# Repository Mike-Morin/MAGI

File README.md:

## 363_Electrode
Electrode array with 3 input neuron contacts, 6 hidden layer contacts, and 3 output neuron contacts with dual input and output contacts for excitatory and inhibitory input and output neurons. Fits on a standard compound microscope stage and supports 12mm round coverslips for the electrode arrays.

## PetriDish
A chemotaxis game to be interfaced with a physical neural network using the Analog Discovery 2 API. Intended to train a network using reinforcement learning. An agent must follow concentration gradients to food in order to replenish energy. You can play it too.

## pnn_cs_driver
A 4 channel precision voltage controlled current source. 1mA/V, biploar 5mA+/-20nA output with 18V compliance voltage, <10ppm, 3.5 MHz bandwdith.

## SMU Test Fixture (In Progress)
16-Channel source measure unit with multiplexer for the Analog Discovery 2 (AD2). Intended to interface with a 32 pin electrode array. 

## SMU Shunt Amp (In Progress)
 - Prototype board for high speed, precision SMU Test Fixture current shunt amp.
 
## 20 Pin Electrode Connector
Pogo pin connector to bare wire. For mounting to a microscope stage and making contact with a microscope slide electrode array. This PCB goes on the stage, slides clip under the pogo pins, and a very flexible wiring harness comes off this board and into your test gear. The idea is to save a lot of money on a probe station microscope combo.

## Electrode Castellated
Microscope slide electrode array utilizing castellations as electrodes. This electrode array provides two independent cavities for testing colloidal neuromorphic devices, or, potentially, real biological neurons (use biocompatible plating such as ENIG gold). This should be epoxied to a glass slide and can be sealed over top with ports for pumping in and out materials. The cutouts allow microscopy while performing electrical excitation and measurement.

Soak FR4 boards in semiconductor grade water for a day to remove contaminant ions if precision measurements are required.

## Precision Rail Splitter
Simple precision rail splitter, currently untested. I find myself needing one of these weirdly often for experiments. The SMU Test Fixture should mostly eliminate this need.
 
## MAGI Symbols, Footprints, Models
KiCad  symbols, footprints, and models.

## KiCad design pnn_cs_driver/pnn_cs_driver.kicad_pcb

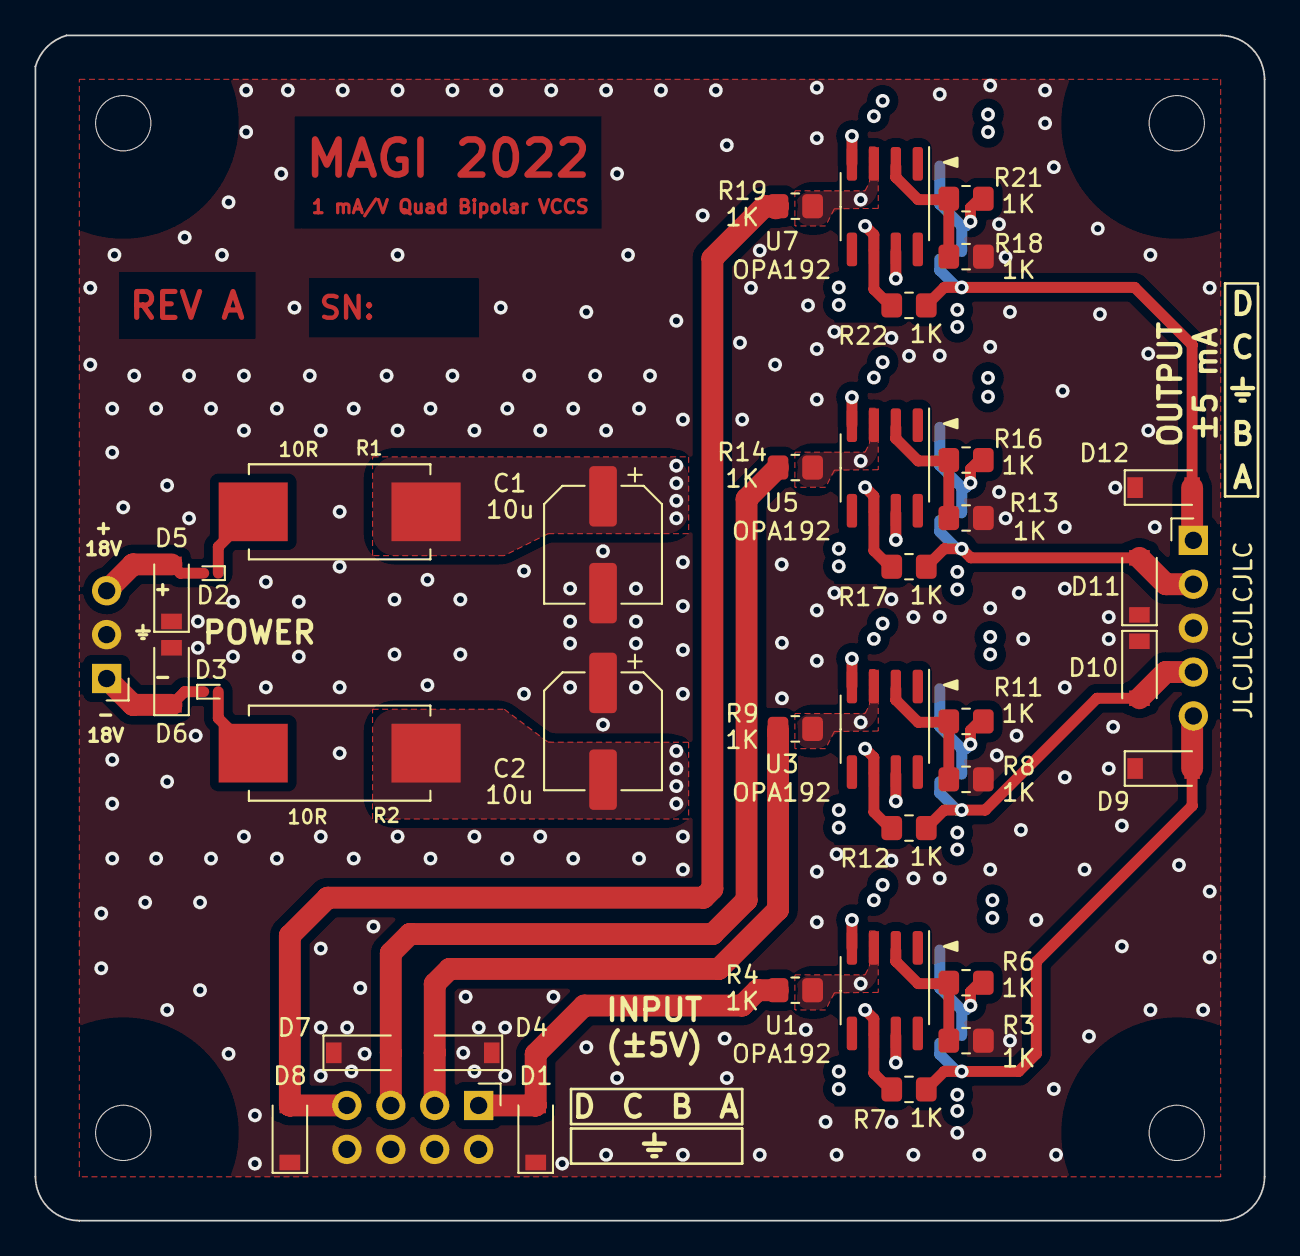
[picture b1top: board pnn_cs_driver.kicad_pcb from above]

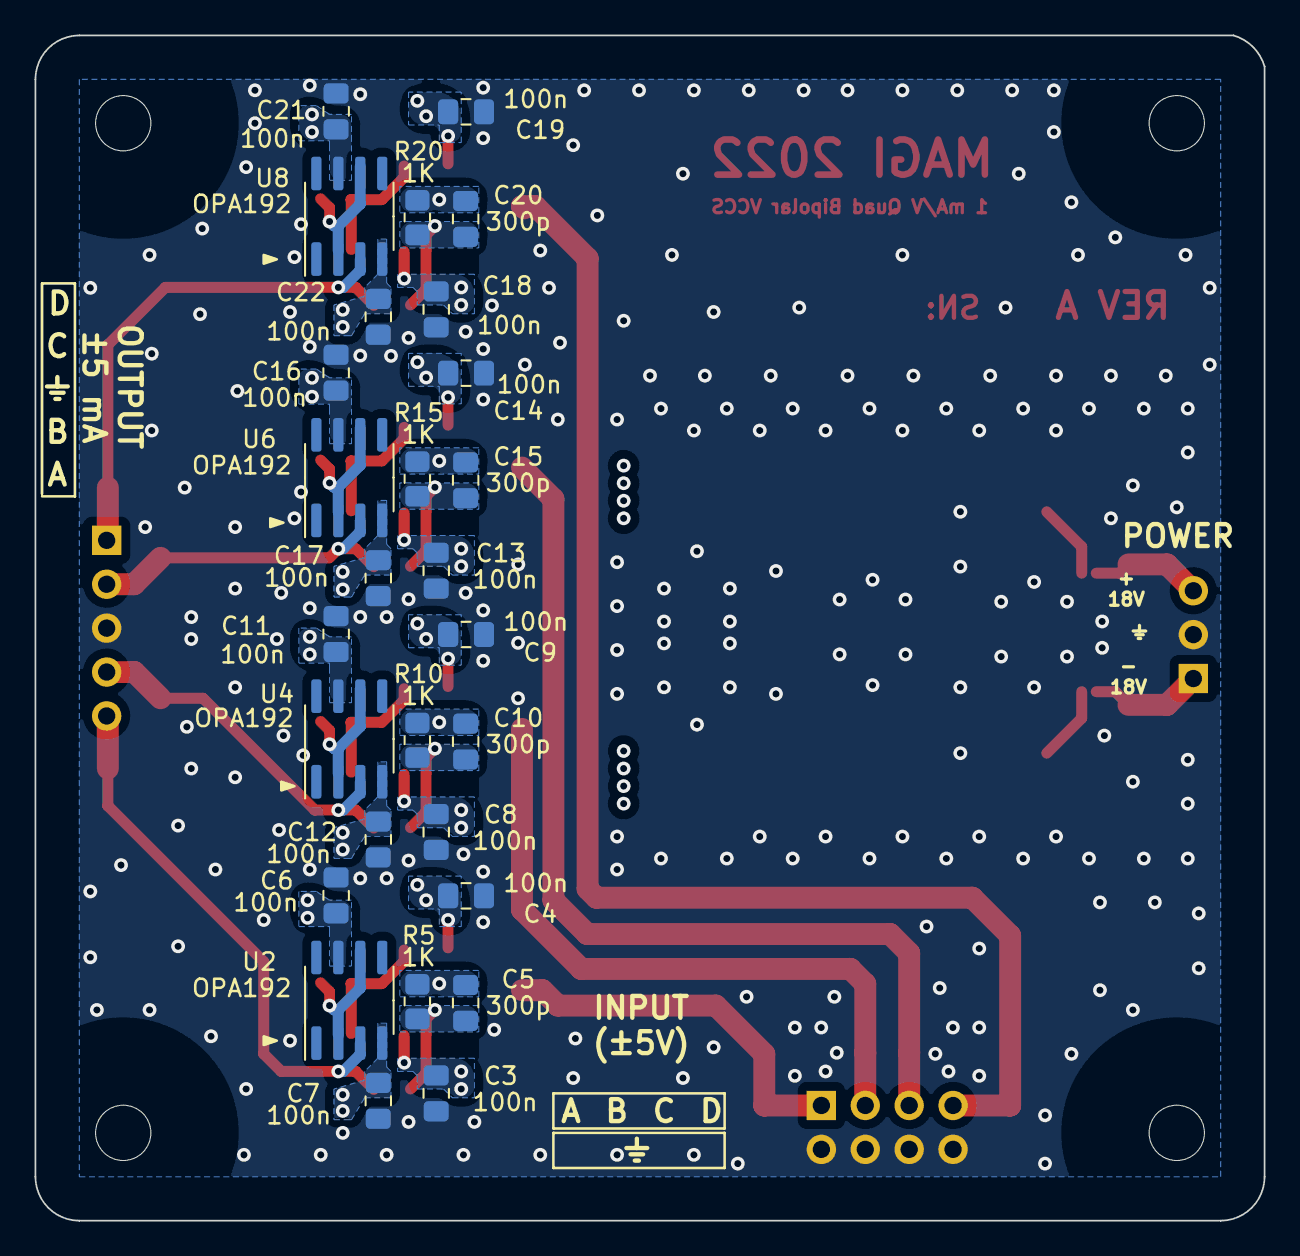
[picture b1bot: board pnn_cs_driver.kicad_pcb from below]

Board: 4 copper layers, 71.1 x 68.6 mm, 71 parts (28 on the bottom side), 31 nets.

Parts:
C1, C2: 10u; CP_Elec_6.3x5.9
C3, C4, C6, C7, C8, C9, C11, C12, C13, C14, C16, C17, C18, C19, C21, C22: 100n; C_0805_2012Metric_Pad1.18x1.45mm_HandSolder
C5, C10, C15, C20: 300p; C_0805_2012Metric_Pad1.18x1.45mm_HandSolder
D1, D4, D5, D6, D7, D8, D9, D10, D11, D12: TVS; D_SOD-123
D2, D3: D_Schottky; D_SOD-923
H1, H2, H3, H4: MountingHole; MountingHole_3.2mm_M3_ISO7380
J1: POWER; PinHeader_1x03_P2.54mm_Horizontal
J2: Conn_02x04_Odd_Even; PinHeader_2x04_P2.54mm_Horizontal
J3: OUTPUT; PinHeader_1x05_P2.54mm_Horizontal
R1, R2: 10R; wirewound_inrush_fp
R3, R4, R5, R6, R7, R8, R9, R10, R11, R12, R13, R14, R15, R16, R17, R18, R19, R20, R21, R22: 1K; R_0805_2012Metric_Pad1.20x1.40mm_HandSolder
U1, U2, U3, U4, U5, U6, U7, U8: OPA192; SOIC-8_3.9x4.9mm_P1.27mm

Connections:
+18V: C1.1, C3.2, C6.2, C8.2, C11.2, C13.2, C16.2, C18.2, C21.2, R1.1, U1.7 (V+), U2.7 (V+), U3.7 (V+), U4.7 (V+), U5.7 (V+), U6.7 (V+), U7.7 (V+), U8.7 (V+)
-18V: C2.2, C4.2, C7.2, C9.2, C12.2, C14.2, C17.2, C19.2, C22.2, R2.1, U1.4 (V-), U2.4 (V-), U3.4 (V-), U4.4 (V-), U5.4 (V-), U6.4 (V-), U7.4 (V-), U8.4 (V-)
GND: C1.2, C2.1, C3.1, C4.1, C6.1, C7.1, C8.1, C9.1, C11.1, C12.1, C13.1, C14.1, C16.1, C17.1, C18.1, C19.1, C21.1, C22.1, D1.1 (A1), D4.1 (A1), D5.1 (A1), D6.2 (A2), D7.1 (A1), D8.1 (A1), D9.1 (A1), D10.1 (A1), D11.1 (A1), D12.1 (A1), J1.2, J2.2, J2.4, J2.6, J2.8, J3.3, R3.1, R8.1, R13.1, R18.1
IN_A: D1.2 (A2), J2.1, R4.1
IN_B: D4.2 (A2), J2.3, R9.1
IN_C: D7.2 (A2), J2.5, R14.1
IN_D: D8.2 (A2), J2.7, R19.1
unnamed: C5.1, R4.2, R5.1, U1.3 (+)
unnamed: C5.2, R5.2, R7.1, U1.6
unnamed: C10.1, R9.2, R10.1, U3.3 (+)
unnamed: C10.2, R10.2, R12.1, U3.6
unnamed: C15.1, R14.2, R15.1, U5.3 (+)
unnamed: C15.2, R15.2, R17.1, U5.6
unnamed: C20.1, R19.2, R20.1, U7.3 (+)
unnamed: C20.2, R20.2, R22.1, U7.6
unnamed: D2.2 (A), D5.2 (A2), J1.3
unnamed: D3.1 (K), D6.1 (A1), J1.1
unnamed: D2.1 (K), R1.2
unnamed: D3.2 (A), R2.2
unnamed: R3.2, R6.1, U1.2 (-)
unnamed: R6.2, U2.2 (-), U2.6
unnamed: R8.2, R11.1, U3.2 (-)
unnamed: R11.2, U4.2 (-), U4.6
unnamed: R13.2, R16.1, U5.2 (-)
unnamed: R16.2, U6.2 (-), U6.6
unnamed: R18.2, R21.1, U7.2 (-)
unnamed: R21.2, U8.2 (-), U8.6
OUT_A: D9.2 (A2), J3.5, R7.2, U2.3 (+)
OUT_B: D10.2 (A2), J3.4, R12.2, U4.3 (+)
OUT_C: D11.2 (A2), J3.2, R17.2, U6.3 (+)
OUT_D: D12.2 (A2), J3.1, R22.2, U8.3 (+)

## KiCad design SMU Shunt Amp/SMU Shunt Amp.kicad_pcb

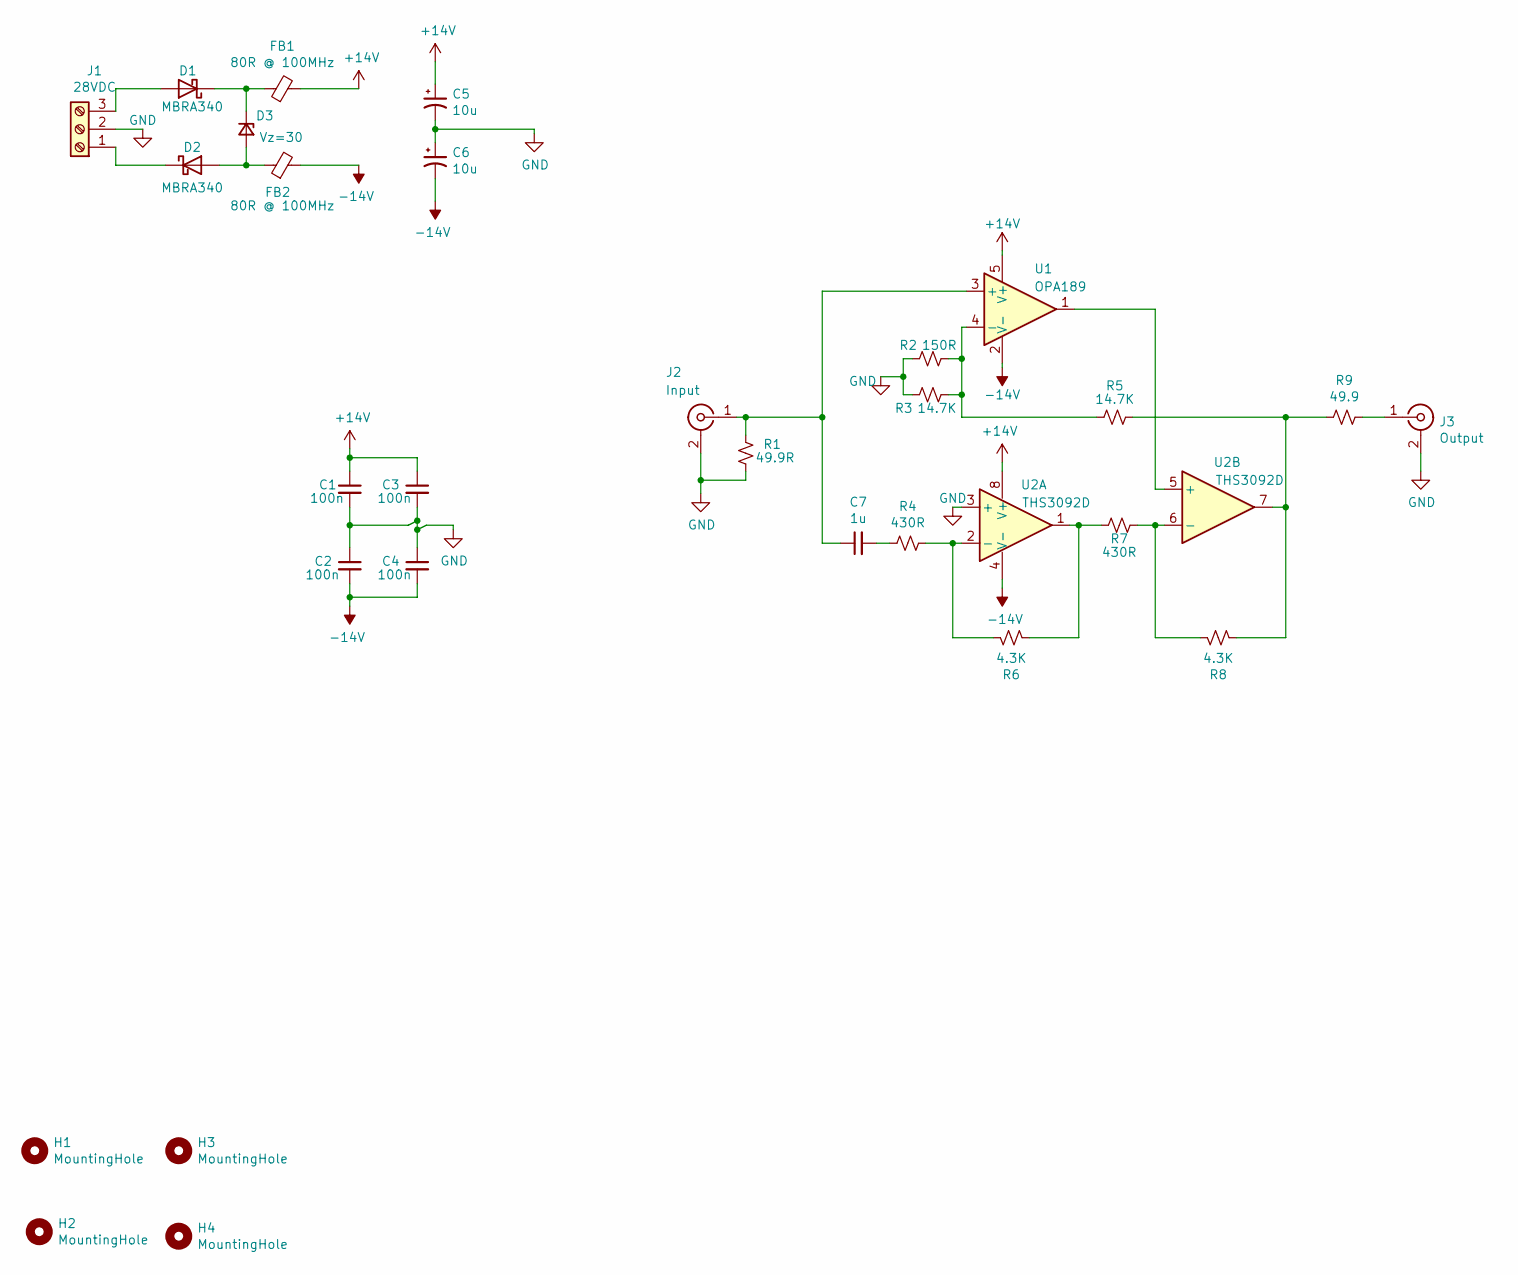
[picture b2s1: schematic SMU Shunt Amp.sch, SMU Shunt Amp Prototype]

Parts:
C1, C2, C3, C4: 100n; C_0805_2012Metric_Pad1.18x1.45mm_HandSolder; Part C0805C103K5GEC7210
C5, C6: 10u; CP_Elec_6.3x7.7; Part UCZ1J100MCS1GS
C7: 1u; C_0805_2012Metric_Pad1.18x1.45mm_HandSolder
D1, D2: MBRA340; D_SMA_Handsoldering
D3: Vz=30; D_SOD-123
FB1, FB2: 80R @ 100MHz; R_1206_3216Metric_Pad1.30x1.75mm_HandSolder
H1, H2, H3, H4: MountingHole; MountingHole_3.2mm_M3
J1: 28VDC; TerminalBlock_Phoenix_PT-1,5-3-5.0-H_1x03_P5.00mm_Horizontal
J2: Input; TE_1-1337445-0; Part 1-1337445-0
J3: Output; TE_1-1337445-0; Part 1-1337445-0
R1: 49.9R; R_0805_2012Metric_Pad1.20x1.40mm_HandSolder; Part CRCW080549R9FKEA
R2: 150R; R_0805_2012Metric_Pad1.20x1.40mm_HandSolder
R3, R5: 14.7K; R_0805_2012Metric_Pad1.20x1.40mm_HandSolder
R4, R7: 430R; R_0805_2012Metric_Pad1.20x1.40mm_HandSolder
R6, R8: 4.3K; R_0805_2012Metric_Pad1.20x1.40mm_HandSolder
R9: 49.9; R_0805_2012Metric_Pad1.20x1.40mm_HandSolder; Part CRCW080549R9FKEA
U1: OPA189; SOT-23-5_HandSoldering; Part OPA189IDBVR
U2: THS3092D; SOIC-8_3.9x4.9mm_P1.27mm

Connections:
+15V: C1.1, C3.1, C5.1, FB1.2, U1.5 (V+), U2.8 (V+)
-15V: C2.2, C4.2, C6.2, FB2.2, U1.2 (V-), U2.4 (V-)
GND: C1.2, C2.1, C3.2, C4.1, C5.2, C6.1, J1.2, J2.2 (Ext), J3.2 (Ext), R1.1, R2.2, R3.2, U2.3 (+)
unnamed: C7.1, J2.1 (In), R1.2, U1.3 (+)
unnamed: C7.2, R4.2
unnamed: D1.1 (K), D3.1 (K), FB1.1
unnamed: D1.2 (A), J1.3
unnamed: D2.1 (K), J1.1
unnamed: D2.2 (A), D3.2 (A), FB2.1
unnamed: J3.1 (In), R9.1
unnamed: R2.1, R3.1, R5.2, U1.4 (-)
unnamed: R4.1, R6.2, U2.2 (-)
unnamed: R5.1, R8.1, R9.2, U2.7
unnamed: R6.1, R7.2, U2.1
unnamed: R7.1, R8.2, U2.6 (-)
unnamed: U1.1, U2.5 (+)

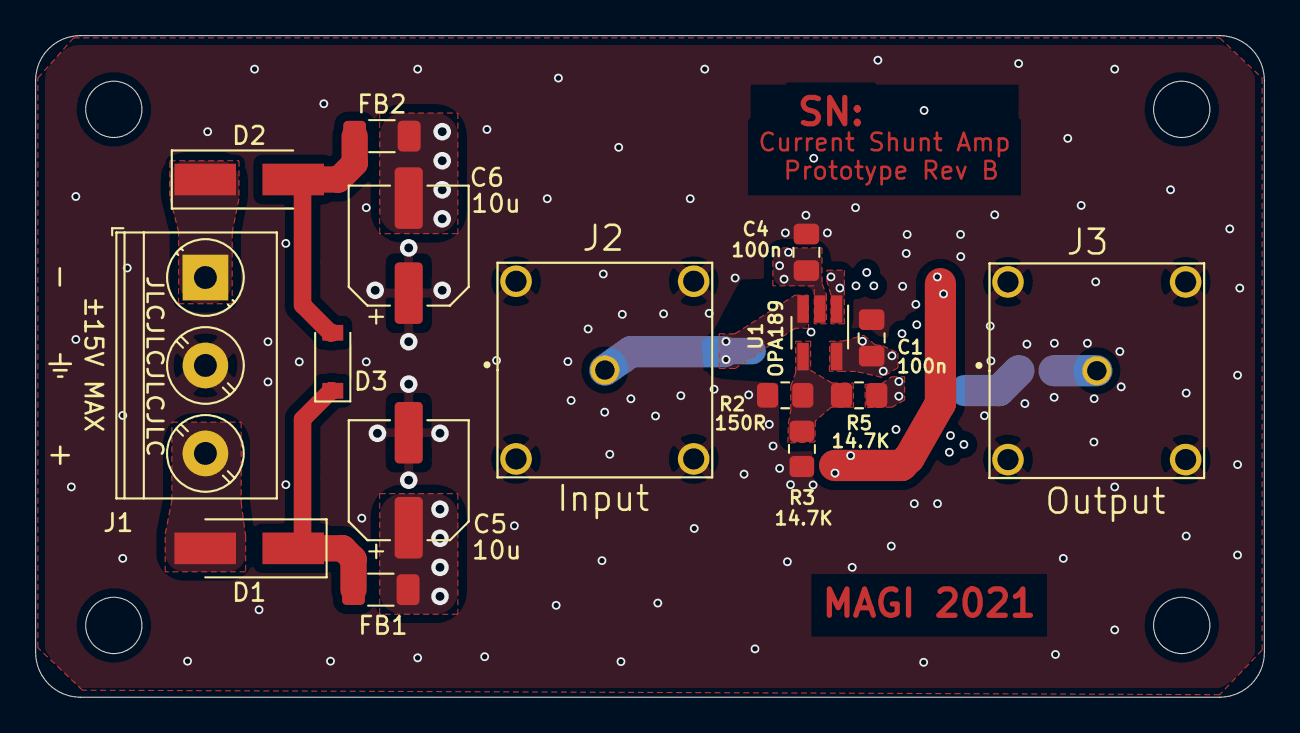
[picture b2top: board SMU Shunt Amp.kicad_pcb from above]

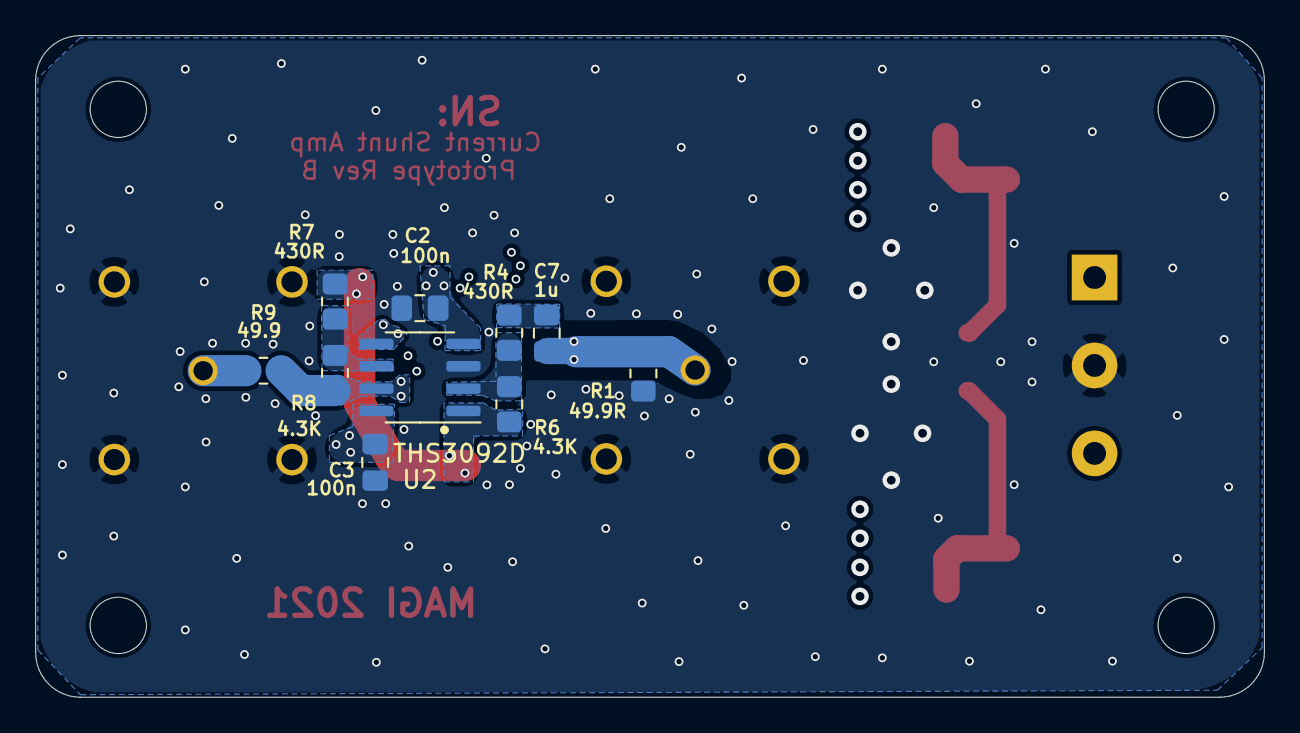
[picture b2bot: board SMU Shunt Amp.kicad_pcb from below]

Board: 4 copper layers, 69.9 x 37.6 mm, 30 parts (10 on the bottom side), 16 nets.

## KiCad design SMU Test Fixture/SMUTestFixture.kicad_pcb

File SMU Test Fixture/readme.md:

## Source Measure Unit Test Fixture

- Characterize nanocolloidal and solid state neuromorphic devices.
  - Measure impedance changes as a result of precise excitation charges and flux-linkages over a large and precise range of excitation input values.
  - Picocoulomb and picovolt-seconds targeted.
  
- Relay multiplexer to interface with up to 16 devices.

- Utilizes Analog Discovery 2 (AD2) for analog measurement and relay control.
  - Aux power and scope input (for pH meter in this project).
  - Provides isolated, clean power for AD2.
  - Exposes AD2 ports for pass-through (AD2 is still useful for other projects).
  - Selectable fully differential and single ended scope modes.
  - "Automatic" AD2 calibration with external multimeter.
  - Internal impedance analyzer shunt resistor selector.
  
 - External excitation and multimeter inputs.

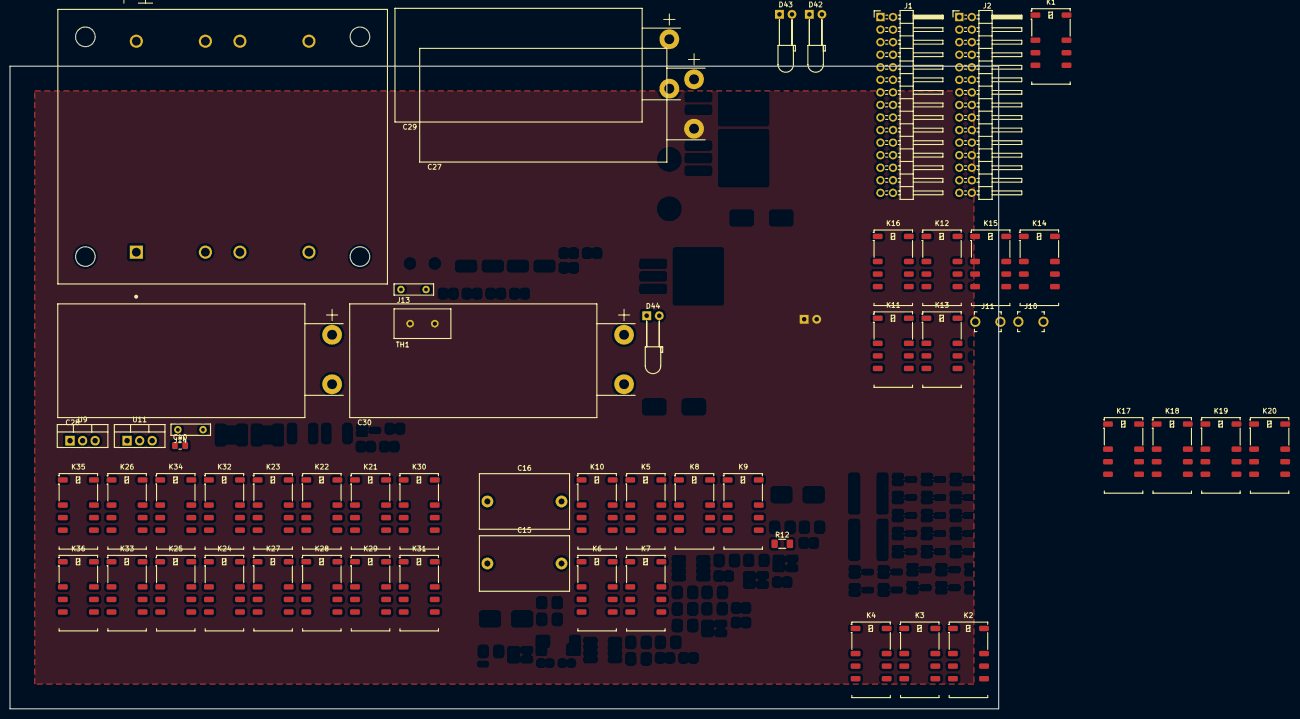
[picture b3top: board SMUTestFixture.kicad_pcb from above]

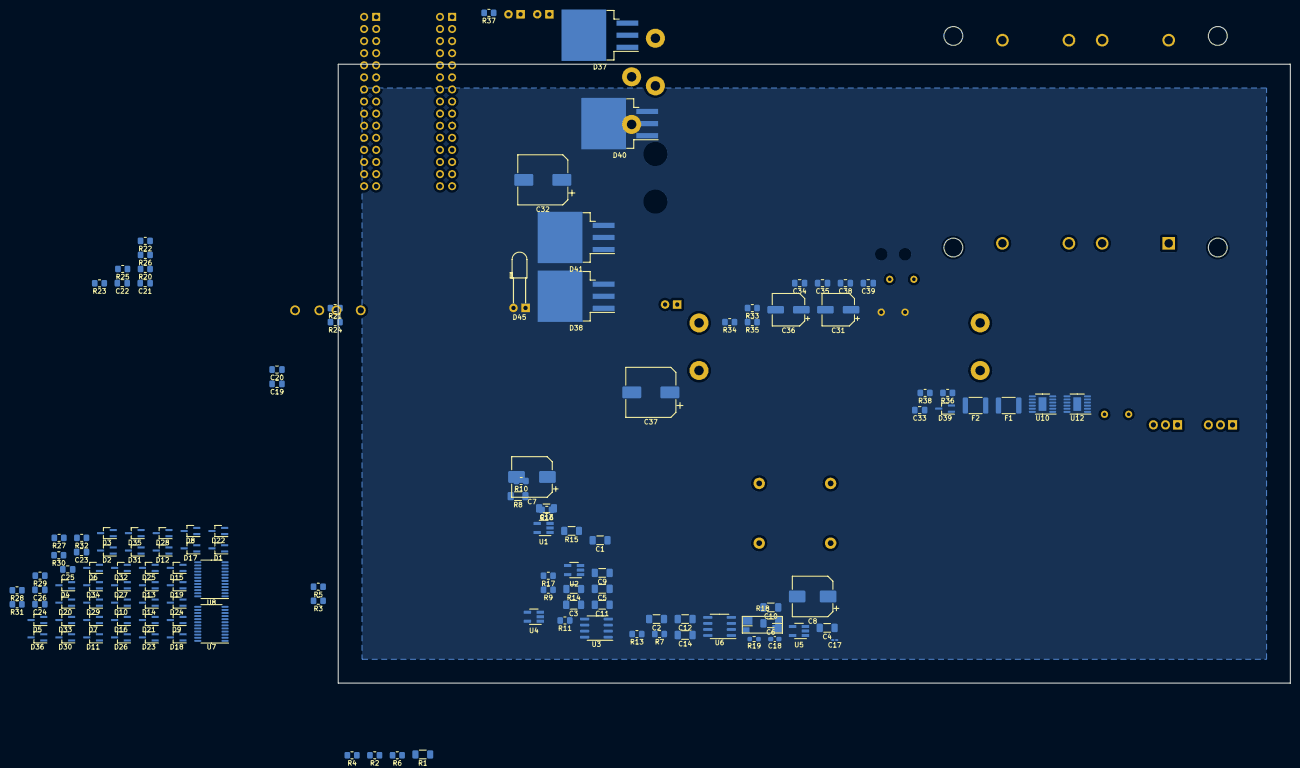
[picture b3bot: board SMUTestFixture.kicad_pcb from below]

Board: 2 copper layers, 200.0 x 130.0 mm, 181 parts (124 on the bottom side), 121 nets, no tracks yet.

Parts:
C1, C2, C3, C4, C5, C6, C9, C10, C11, C12, C13, C14: 100n; C_1206_3216Metric_Pad1.33x1.80mm_HandSolder
C7, C8: 100u; CP_Elec_8x10
C15, C16: 1u; C_Rect_L18.0mm_W11.0mm_P15.00mm_FKS3_FKP3
C17: 33p; C_0201_0603Metric_Pad0.64x0.40mm_HandSolder
C18: 6.2p; C_0603_1608Metric_Pad1.08x0.95mm_HandSolder
C19, C20, C21, C22: C_Small; C_0805_2012Metric_Pad1.18x1.45mm_HandSolder
C23, C24, C25, C26, C33, C39: 10u; C_0805_2012Metric_Pad1.18x1.45mm_HandSolder
C27, C28, C29, C30: 4.7m; d=22_L=50_Radial_Horiz_P=10
C31, C36: 10u; CP_Elec_6.3x5.8
C32, C37: 150u; CP_Elec_10x10
C34, C40: 4.7u; C_0805_2012Metric_Pad1.18x1.45mm_HandSolder
C35, C38: 22u; C_0805_2012Metric_Pad1.18x1.45mm_HandSolder
D1, D2, D3, D4, D5, D6, D7, D8, D9, D10, D11, D12, D13, D14, D15, D16, D17, D18, D19, D20, D21, D22, D23, D24, D25, D26, D27, D28, D29, D30, D31, D32, D33, D34, D35, D36: Vz=+-15V; SOT-323_SC-70_Handsoldering
D37, D38, D40, D41: D; TO-263-3_TabPin2
D39: 20V Clamp; SOT-323_SC-70_Handsoldering
D42, D43, D44, D45: LED; LED_D3.0mm_Horizontal_O6.35mm_Z2.0mm
F1, F2: 1 A; Fuse_1812_4532Metric
J1, J2: AD2 Connector; PinHeader_2x15_P2.54mm_Horizontal
J10, J11: 105-1102-001; Test_Jack_Horiz
J13: Hot_Spade; p250_spade
J14: Neutral_Spade; p250_spade
K1: External Source Enable; Relay_DPDT_Kemet_EE2_NUH
K2, K3, K4, K21, K22, K23, K24, K25, K26, K27, K28, K29, K30, K31, K32, K33, K34, K35, K36: EC2-12SNU; Relay_DPDT_Kemet_EE2_NUH
K5: Integrator Reset; Relay_DPDT_Kemet_EE2_NUH
K6: I/V Mode Select; Relay_DPDT_Kemet_EE2_NUH
K7: 3x Gain Enable; Relay_DPDT_Kemet_EE2_NUH
K8: Shunt Select; Relay_DPDT_Kemet_EE2_NUH
K9: Shunt/Sense Select; Relay_DPDT_Kemet_EE2_NUH
K10: Sense Select; Relay_DPDT_Kemet_EE2_NUH
K11: 50 Ohm Ena; Relay_DPDT_Kemet_EE2_NUH
K12: Single/Diff Switch; Relay_DPDT_Kemet_EE2_NUH
K13: AC/DC Couple; Relay_DPDT_Kemet_EE2_NUH
K14: AC/DC Couple A; Relay_DPDT_Kemet_EE2_NUH
K15: Ext Meas Sel B; Relay_DPDT_Kemet_EE2_NUH
K16: Ext Meas Sel A; Relay_DPDT_Kemet_EE2_NUH
K17: 6x1 Mux Sel A; Relay_DPDT_Kemet_EE2_NUH
K18: 6x1 Mux Sel B; Relay_DPDT_Kemet_EE2_NUH
K19, K20: 6x1 Mux Sel C; Relay_DPDT_Kemet_EE2_NUH
R1, R8, R12: 1M; R_1206_3216Metric_Pad1.30x1.75mm_HandSolder
R2: 100K; R_0805_2012Metric_Pad1.20x1.40mm_HandSolder
R3, R17: 10K; R_0805_2012Metric_Pad1.20x1.40mm_HandSolder
R4: 1K; R_0805_2012Metric_Pad1.20x1.40mm_HandSolder
R5: 100R; R_0805_2012Metric_Pad1.20x1.40mm_HandSolder
R6, R16: 10R; R_0805_2012Metric_Pad1.20x1.40mm_HandSolder
R7, R10: 5K; R_0805_2012Metric_Pad1.20x1.40mm_HandSolder
R9: 56K; R_0805_2012Metric_Pad1.20x1.40mm_HandSolder
R11: 11.8K; R_0805_2012Metric_Pad1.20x1.40mm_HandSolder
R13: 5.9K; R_0805_2012Metric_Pad1.20x1.40mm_HandSolder
R14, R15: 14.7K; R_1206_3216Metric_Pad1.30x1.75mm_HandSolder
R18: 0R01; CSM_Vishay_Shunt_4term
R19: 150R; R_0603_1608Metric_Pad0.98x0.95mm_HandSolder
R20, R21, R22: 49.9R; R_0805_2012Metric_Pad1.20x1.40mm_HandSolder
R23, R24, R25, R26: 27M; R_0805_2012Metric_Pad1.20x1.40mm_HandSolder
R27: 2.430K; R_0805_2012Metric_Pad1.20x1.40mm_HandSolder
R28, R30, R31, R32: 270; R_0805_2012Metric_Pad1.20x1.40mm_HandSolder
R29: 1.150K; R_0805_2012Metric_Pad1.20x1.40mm_HandSolder
R33: 270R; R_0805_2012Metric_Pad1.20x1.40mm_HandSolder
R34, R38: 750R; R_0805_2012Metric_Pad1.20x1.40mm_HandSolder
R35, R37: 150k; R_0805_2012Metric_Pad1.20x1.40mm_HandSolder
R36: 620R; R_0805_2012Metric_Pad1.20x1.40mm_HandSolder
T1: VPP28-1060; XFMR_VPP28-1060
TH1: 3.5A max <130C; NTC d=11.5 p=5mm w=6mm
U1, U4: OPA192; SOT-23-5_HandSoldering
U2, U5: OPA189; SOT-23-5_HandSoldering
U3: OPA551U; SOIC-8_3.9x4.9mm_P1.27mm
U6: OPA1611; SOIC-8_3.9x4.9mm_P1.27mm
U7, U8: ADG1414BRU; TSSOP-24_4.4x7.8mm_P0.65mm
U9: LT1086-5.0; TO-220-3_Vertical
U10: LT3045xMSE-1; MSOP-12-1EP_3x4mm_P0.65mm_EP1.65x2.85mm
U11: LT1086-12; TO-220-3_Vertical
U12: LT3094xMSE; MSOP-12-1EP_3x4mm_P0.65mm_EP1.65x2.85mm

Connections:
3x_gain_en_r: D1.3, D2.3, D3.3, D4.3, D5.3, D6.3, K1.12, K2.12, K3.12, K4.12, K7.12, K8.12, U8.5
3x_gain_en_s: D2.2, D8.2, D14.2, D20.2, D26.2, D32.2, K7.1, K11.1, K17.1, K23.1, K29.1, K35.1, U7.14
+3V8: R27.2, R29.1, U7.23, U8.23
+5V: C32.1, D42.2, U9.2
+12V: C37.1, D44.2, R27.1, R28.2, R31.2, U11.2
+15V: C1.1, C2.1, C3.1, C4.1, C5.1, C6.1, C7.1, C23.1, C24.1, C33.1, D43.2, U1.4, U2.4, U3.7, U4.4, U5.4, U6.4, U7.2, U8.2, U10.10, U10.11
-15V: C8.2, C9.2, C10.2, C11.2, C12.2, C13.2, C14.2, C25.2, C26.2, C39.2, D45.1, U1.5, U2.5, U3.1, U3.4, U3.5, U4.5, U5.5, U6.5, U7.21, U8.21, U12.10, U12.11, U12.12
/Ammeter and Charge Integrator/IV_src_output: K1.5, U3.6
/Ammeter and Charge Integrator/ammeter_input: K9.4, R1.1, R2.1, R3.1, R4.1, R5.1, R6.1
/Ammeter and Charge Integrator/ammeter_meas_output: C18.1, K17.8, R12.2, R15.1, U6.3
/Ammeter and Charge Integrator/ammeter_output: K6.10, K8.8, K10.8, K20.3, K21.8, K22.8, K23.8, K24.8, K25.8, K26.8, K27.8, K28.8, K29.8, K30.8, K31.8, K32.8, K33.8, K34.8, K35.8, K36.8, R8.2, R16.2, R17.2, R18.3, R18.4
/Ammeter and Charge Integrator/charge_int_output: C16.1, K17.10, R10.2, U4.3
/DIO_0: J1.15, J2.15, U7.3
/DIO_1: J1.13, J2.13, U7.1, U8.1
/DIO_2: J1.11, J2.11, U7.24, U8.24
/DIO_3: J1.9, J2.9
/DIO_4: J1.7, J2.7
/DIO_5: J1.5, J2.5
/DIO_6: J1.3, J2.3
/DIO_7: J1.1, J2.1
/DIO_8: J1.16, J2.16
/DIO_9: J1.14, J2.14
/DIO_10: J1.12, J2.12
/DIO_11: J1.10, J2.10
/DIO_12: J1.8, J2.8
/DIO_13: J1.6, J2.6
/DIO_14: J1.4, J2.4
/DIO_15: J1.2, J2.2
/Impedance Analyzer/impa_input: K1.4, K4.4, K17.3
/Power Supplies/unreg_neg_18VDC: C29.2, C30.2, C40.2, D39.2, D40.2, D41.2, U12.1, U12.2, U12.3, U12.5, U12.13
/Power Supplies/unreg_pos_18VDC: C27.1, C28.1, C31.1, C34.1, C36.1, D37.1, D38.1, D39.1, U9.3, U10.1, U10.4, U10.7, U11.3
/Relay Driver/sd_a_to_b: U7.22, U8.3
/Scope Meas Selector/input_2a: C15.1, K17.5, R7.2, U1.3
/ad2_cal_scope_p: K16.9, K19.8, K20.8
/ext_meas_dut: C22.2, J1.27, K14.8, K15.3, K20.4, K20.9
/ext_meas_phiqi: C21.2, J1.29, K14.5, K15.5, K19.4, K19.9
/ext_source: K1.3, R21.2
/ps_n: J1.24, J2.24
/ps_p: J1.23, J2.23
/scope_1_n: C19.2, J1.30, K12.4, K13.5
/scope_2_n: C20.2, J1.28, K12.9, K13.8
/trig_1: J1.17, J2.17
/trig_2: J1.18, J2.18
/wg_1: J1.21, K11.5, K15.8, K16.8, R9.1, R20.2, U2.1
/wg_2: J1.22, K11.8, K15.10, R22.2
GND: C1.2, C2.2, C3.2, C4.2, C5.2, C6.2, C7.2, C8.1, C9.1, C10.1, C11.1, C12.1, C13.1, C14.1, C17.2, C23.2, C24.2, C25.1, C26.1, C27.2, C28.2, C29.1, C30.1, C31.2, C32.2, C33.2, C34.2, C35.2, C36.2, C37.2, C38.1, C39.1, C40.1, D39.3, J1.19, J1.20, J1.25, J1.26, J2.19, J2.20, J2.25, J2.26, J11.1, K12.5, K12.8, K16.10, K21.5, K22.5, K23.5, K24.5, K25.5, K26.5, K27.5, K28.5, K29.5, K30.5, K31.5, K32.5, K33.5, K34.5, K35.5, K36.5, R9.2, R13.2, R14.2, R19.2, R23.2, R24.2, R25.2, R26.2, R29.2, R30.2, R32.2, R33.2, R34.2, R35.2, R36.2, R37.1, R38.1, T1.12, U1.1, U4.1, U6.2, U7.4, U8.4, U9.1, U10.6, U10.9, U11.1, U12.6, U12.9
unnamed: C15.2, K5.3, R8.1, U1.2
unnamed: C16.2, K5.10, R12.1, U4.2
unnamed: C17.1, K7.4, R11.1, U2.2, U3.2
unnamed: C18.2, R14.1, R15.2, R19.1, U5.2
unnamed: C19.1, K13.3
unnamed: C20.1, K13.10
unnamed: C21.1, K14.3
unnamed: C22.1, K14.10
unnamed: C35.1, R35.1, U10.8
unnamed: C38.2, R37.2, U12.8
unnamed: D37.2, D40.1, F1.1
unnamed: D38.2, D41.1, F2.1
unnamed: D42.1, R33.1
unnamed: D43.1, R34.1
unnamed: D44.1, R36.1
unnamed: D45.2, R38.2
unnamed: F1.2, T1.7, T1.10
unnamed: F2.2, T1.9
unnamed: K13.4, R23.1
unnamed: K13.9, R24.1
unnamed: K14.4, R25.1
unnamed: J10.1, K16.4
unnamed: K14.9, R26.1
unnamed: J13.1, TH1.2
unnamed: J14.1, T1.3, T1.6
unnamed: K2.3, R1.2
unnamed: K2.4, K3.3
unnamed: K2.5, R2.2
unnamed: K2.8, R4.2
unnamed: K2.9, K3.5
unnamed: K2.10, R3.2
unnamed: K3.4, K4.3
unnamed: K3.8, R6.2
unnamed: K3.9, K4.5
unnamed: K3.10, R5.2
unnamed: K5.4, K5.5, R7.1
unnamed: K5.8, K5.9, R10.1
unnamed: K6.8, K9.9, U5.1
unnamed: K6.9, R11.2
unnamed: K7.5, R13.1
unnamed: K8.3, R18.1
unnamed: K8.4, K9.3
unnamed: K8.9, K9.5
unnamed: K10.3, R18.2
unnamed: K9.10, K10.4
unnamed: K8.5, K10.5, R16.1
unnamed: K9.8, K10.9
unnamed: K8.10, K10.10, R17.1
unnamed: K11.3, R20.1
unnamed: K11.10, R22.1
unnamed: K15.4, K16.3
unnamed: K15.9, K16.5
unnamed: K17.4, K18.3
unnamed: K17.9, K18.5
unnamed: K18.4, K19.3
unnamed: K18.9, K19.5
unnamed: R28.1, U7.18
unnamed: R30.1, U7.20
unnamed: R31.1, U8.18
unnamed: R32.1, U8.20
unnamed: T1.1, T1.4, TH1.1
unnamed: U2.3, U3.3
unnamed: U5.3, U6.1
unnamed: U7.6, U7.8, U7.10, U7.12, U7.13, U7.15, U7.17, U7.19
unnamed: U8.6, U8.8, U8.10, U8.12, U8.13, U8.15, U8.17, U8.19
cur_volt_mode_sel_r: D7.3, D8.3, D9.3, D10.3, D11.3, D12.3, K5.12, K6.12, K9.12, K10.12, K11.12, K15.12, U8.7
cur_volt_mode_sel_s: D5.2, D11.2, D17.2, D23.2, D29.2, D35.2, K4.1, K6.1, K12.1, K20.1, K26.1, K32.1, U7.7
dut_sel_1_r: D19.3, D20.3, D21.3, D22.3, D23.3, D24.3, K19.12, K20.12, K21.12, K22.12, K23.12, K24.12, U8.11
dut_sel_10_r: D25.3, D26.3, D27.3, D28.3, D29.3, D30.3, K25.12, K26.12, K27.12, K28.12, K29.12, K30.12, U8.14
dut_sel_10_s: D1.2, D7.2, D13.2, D19.2, D25.2, D31.2, K8.1, K15.1, K18.1, K24.1, K30.1, K36.1, U7.16
dut_sel_11_r: D31.3, D32.3, D33.3, D34.3, D35.3, D36.3, K31.12, K32.12, K33.12, K34.12, K35.12, K36.12, U8.16
dut_sel_11_s: D6.2, D12.2, D18.2, D24.2, D30.2, D36.2, K1.1, K9.1, K16.1, K19.1, K25.1, K31.1, U7.5
dut_sel_13_s: D4.2, D10.2, D16.2, D22.2, D28.2, D34.2, K3.1, K10.1, K13.1, K21.1, K27.1, K33.1, U7.9
dut_sel_14_s: D3.2, D9.2, D15.2, D21.2, D27.2, D33.2, K2.1, K5.1, K14.1, K22.1, K28.1, K34.1, U7.11
ext_acdc_n_r: D13.3, D14.3, D15.3, D16.3, D17.3, D18.3, K12.12, K13.12, K14.12, K16.12, K17.12, K18.12, U8.9
